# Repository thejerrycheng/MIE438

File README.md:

# MIE438_LED_cubic_console! 

This is an instruction of how to setup your own 8 by 8 by 8 LED game console. As there are tons of build-videos out there on YouTube. 

This report will only focus on the circuit design and the software aspect on how to light up the cube. Those two aspects were the consierably most challenging parts of the projects. 

In addition, it will walk through the two games created for the cube: Snake and Pong, two most classic console games of all time! (BUT in 3D!)

Lots of embedded system to be discovered. Let's dive into the lowest levels!

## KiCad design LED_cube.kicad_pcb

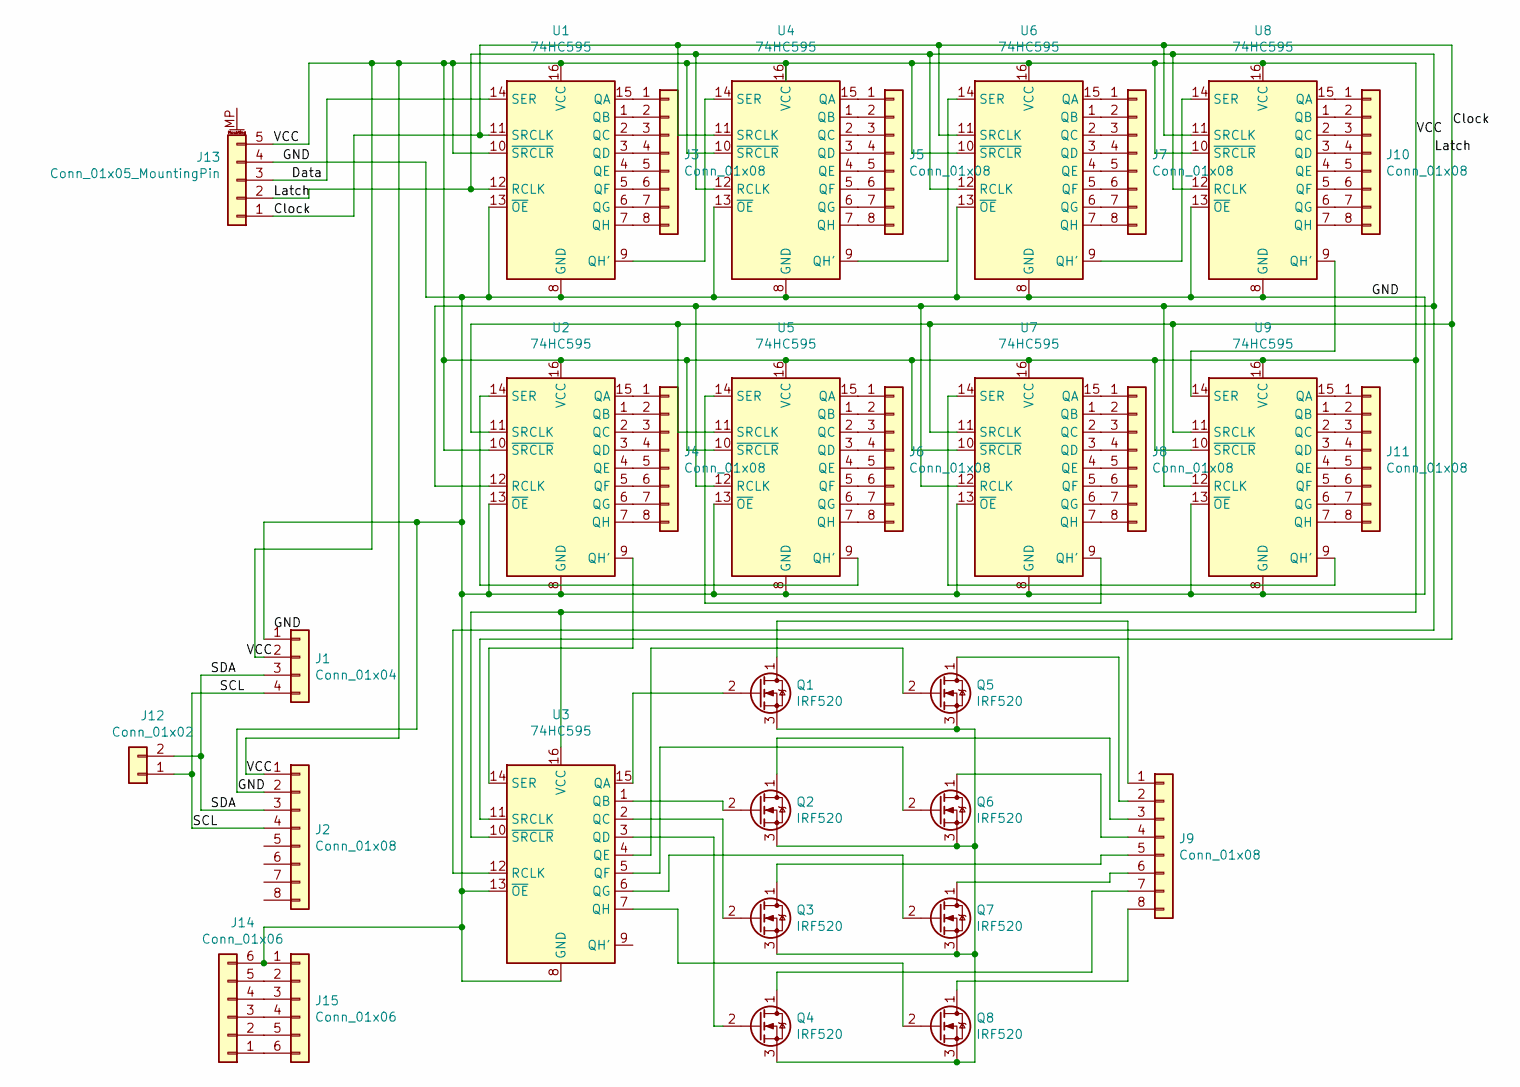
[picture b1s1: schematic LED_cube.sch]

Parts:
J1: Conn_01x04; PinSocket_1x04_P2.54mm_Vertical
J2, J3, J4, J5, J6, J7, J8, J9, J10, J11: Conn_01x08; PinSocket_1x08_P2.54mm_Vertical
J12: Conn_01x02; PinSocket_1x02_P2.54mm_Vertical
J13: Conn_01x05_MountingPin; PinSocket_1x05_P2.54mm_Vertical
J14, J15: Conn_01x06; PinSocket_1x06_P2.54mm_Vertical
Q1, Q2, Q4, Q7, Q8: IRF520; TO-262-3-1EP_Horizontal_TabDown
Q3: IRF520; DirectFET_MX
Q5, Q6: IRF520; TO-251-3-1EP_Horizontal_TabDown
U1, U2, U3, U4, U5, U6, U7, U8, U9: 74HC595; DIP-16_W7.62mm_Socket

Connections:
/Clock: J13.1, U1.11 (SRCLK), U2.11 (SRCLK), U3.11 (SRCLK), U4.11 (SRCLK), U5.11 (SRCLK), U6.11 (SRCLK), U7.11 (SRCLK), U8.11 (SRCLK), U9.11 (SRCLK)
/Data: J13.3, U1.14 (SER)
/GND: J1.1, J2.2, J13.4, J14.6, J15.1, U1.8 (GND), U1.13 (~OE), U2.8 (GND), U2.13 (~OE), U3.8 (GND), U3.13 (~OE), U4.8 (GND), U4.13 (~OE), U5.8 (GND), U5.13 (~OE), U6.8 (GND), U6.13 (~OE), U7.8 (GND), U7.13 (~OE), U8.8 (GND), U8.13 (~OE), U9.8 (GND), U9.13 (~OE)
/Latch: J13.2, U1.12 (RCLK), U2.12 (RCLK), U3.12 (RCLK), U4.12 (RCLK), U5.12 (RCLK), U6.12 (RCLK), U7.12 (RCLK), U8.12 (RCLK), U9.12 (RCLK)
/SCL: J1.4, J2.4, J12.1
/SDA: J1.3, J2.3, J12.2
/VCC: J1.2, J2.1, J13.5, U1.10 (~SRCLR), U1.16 (VCC), U2.10 (~SRCLR), U2.16 (VCC), U3.10 (~SRCLR), U3.16 (VCC), U4.10 (~SRCLR), U4.16 (VCC), U5.10 (~SRCLR), U5.16 (VCC), U6.10 (~SRCLR), U6.16 (VCC), U7.10 (~SRCLR), U7.16 (VCC), U8.10 (~SRCLR), U8.16 (VCC), U9.10 (~SRCLR), U9.16 (VCC)
unnamed: J3.1, U1.15 (QA)
unnamed: J3.2, U1.1 (QB)
unnamed: J3.3, U1.2 (QC)
unnamed: J3.4, U1.3 (QD)
unnamed: J3.5, U1.4 (QE)
unnamed: J3.6, U1.5 (QF)
unnamed: J3.7, U1.6 (QG)
unnamed: J3.8, U1.7 (QH)
unnamed: J4.1, U2.15 (QA)
unnamed: J4.2, U2.1 (QB)
unnamed: J4.3, U2.2 (QC)
unnamed: J4.4, U2.3 (QD)
unnamed: J4.5, U2.4 (QE)
unnamed: J4.6, U2.5 (QF)
unnamed: J4.7, U2.6 (QG)
unnamed: J4.8, U2.7 (QH)
unnamed: J5.1, U4.15 (QA)
unnamed: J5.2, U4.1 (QB)
unnamed: J5.3, U4.2 (QC)
unnamed: J5.4, U4.3 (QD)
unnamed: J5.5, U4.4 (QE)
unnamed: J5.6, U4.5 (QF)
unnamed: J5.7, U4.6 (QG)
unnamed: J5.8, U4.7 (QH)
unnamed: J6.1, U5.15 (QA)
unnamed: J6.2, U5.1 (QB)
unnamed: J6.3, U5.2 (QC)
unnamed: J6.4, U5.3 (QD)
unnamed: J6.5, U5.4 (QE)
unnamed: J6.6, U5.5 (QF)
unnamed: J6.7, U5.6 (QG)
unnamed: J6.8, U5.7 (QH)
unnamed: J7.1, U6.15 (QA)
unnamed: J7.2, U6.1 (QB)
unnamed: J7.3, U6.2 (QC)
unnamed: J7.4, U6.3 (QD)
unnamed: J7.5, U6.4 (QE)
unnamed: J7.6, U6.5 (QF)
unnamed: J7.7, U6.6 (QG)
unnamed: J7.8, U6.7 (QH)
unnamed: J8.1, U7.15 (QA)
unnamed: J8.2, U7.1 (QB)
unnamed: J8.3, U7.2 (QC)
unnamed: J8.4, U7.3 (QD)
unnamed: J8.5, U7.4 (QE)
unnamed: J8.6, U7.5 (QF)
unnamed: J8.7, U7.6 (QG)
unnamed: J8.8, U7.7 (QH)
unnamed: J9.1, Q1.1 (D)
unnamed: J9.2, Q5.1 (D)
unnamed: J9.3, Q2.1 (D)
unnamed: J9.4, Q6.1 (D)
unnamed: J9.5, Q3.1 (D)
unnamed: J9.6, Q7.1 (D)
unnamed: J9.7, Q4.1 (D)
unnamed: J9.8, Q8.1 (D)
unnamed: J10.1, U8.15 (QA)
unnamed: J10.2, U8.1 (QB)
unnamed: J10.3, U8.2 (QC)
unnamed: J10.4, U8.3 (QD)
unnamed: J10.5, U8.4 (QE)
unnamed: J10.6, U8.5 (QF)
unnamed: J10.7, U8.6 (QG)
unnamed: J10.8, U8.7 (QH)
unnamed: J11.1, U9.15 (QA)
unnamed: J11.2, U9.1 (QB)
unnamed: J11.3, U9.2 (QC)
unnamed: J11.4, U9.3 (QD)
unnamed: J11.5, U9.4 (QE)
unnamed: J11.6, U9.5 (QF)
unnamed: J11.7, U9.6 (QG)
unnamed: J11.8, U9.7 (QH)
unnamed: J14.1, J15.6
unnamed: J14.2, J15.5
unnamed: J14.3, J15.4
unnamed: J14.4, J15.3
unnamed: J14.5, J15.2
unnamed: Q1.2 (G), U3.15 (QA)
unnamed: Q1.3 (S), Q2.3 (S), Q3.3 (S), Q4.3 (S), Q5.3 (S), Q6.3 (S), Q7.3 (S), Q8.3 (S)
unnamed: Q2.2 (G), U3.1 (QB)
unnamed: Q3.2 (G), U3.2 (QC)
unnamed: Q4.2 (G), U3.3 (QD)
unnamed: Q5.2 (G), U3.4 (QE)
unnamed: Q6.2 (G), U3.5 (QF)
unnamed: Q7.2 (G), U3.6 (QG)
unnamed: Q8.2 (G), U3.7 (QH)
unnamed: U1.9 (QH'), U4.14 (SER)
unnamed: U2.9 (QH'), U3.14 (SER)
unnamed: U2.14 (SER), U5.9 (QH')
unnamed: U4.9 (QH'), U6.14 (SER)
unnamed: U5.14 (SER), U7.9 (QH')
unnamed: U6.9 (QH'), U8.14 (SER)
unnamed: U7.14 (SER), U9.9 (QH')
unnamed: U8.9 (QH'), U9.14 (SER)

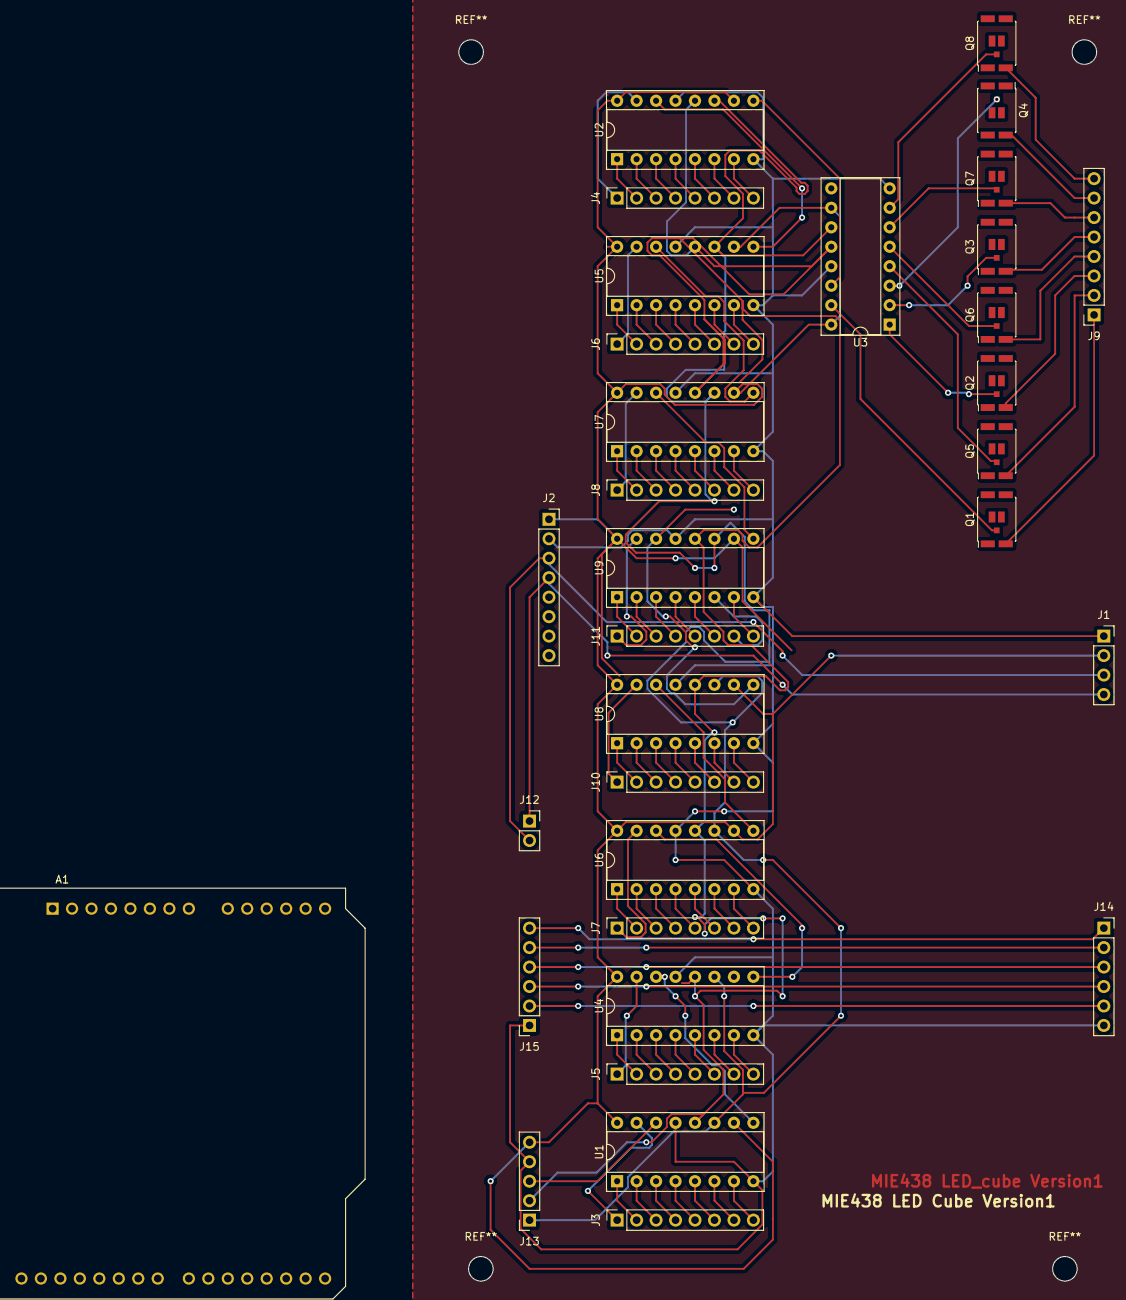
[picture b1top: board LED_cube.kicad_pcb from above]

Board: 2 copper layers, 33 parts (0 on the bottom side), 101 nets.

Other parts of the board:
A1: Arduino_UNO_R2

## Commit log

2022-04-09 Created using Colaboratory
2022-04-12 First Version of the LED Cubic Console
    With animation effects added (six in total); and a 3D snake game!
    Still to be debugged but the game is very playable
    The user controls the snake using two joysticks -- constant pulling
    The cube is rendered every 300us
    Refresh rate of the game can be easily changed and the default is set as 0.4s per frame.
2022-04-12 Animation Effects
2022-04-12 Descriptions on the hardware and software design
2022-04-14 LED Snake Game Version2
2022-04-14 LED Pong Game Version1
2022-04-14 Report on the project
2022-04-14 Circuit Designs
2022-04-14 I/O Response from PS2 controller and OLED
